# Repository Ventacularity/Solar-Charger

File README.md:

# Solar Charger

Solar-powered Li-ion charging and power management system implemented on a custom PCB.

## Overview
This project focuses on hardware design for managing variable solar input while safely charging a Li-ion battery and delivering regulated power rails. The system integrates dedicated charge controllers, buck/boost DC-DC converters, and an ESP32 for monitoring and control.

## Key Features
- Custom PCB design for solar-powered Li-ion charging
- Buck and boost DC-DC converters for regulated 5 V and 3.3 V outputs
- Battery voltage/current sensing and power-path management
- ESP32-based monitoring and control logic

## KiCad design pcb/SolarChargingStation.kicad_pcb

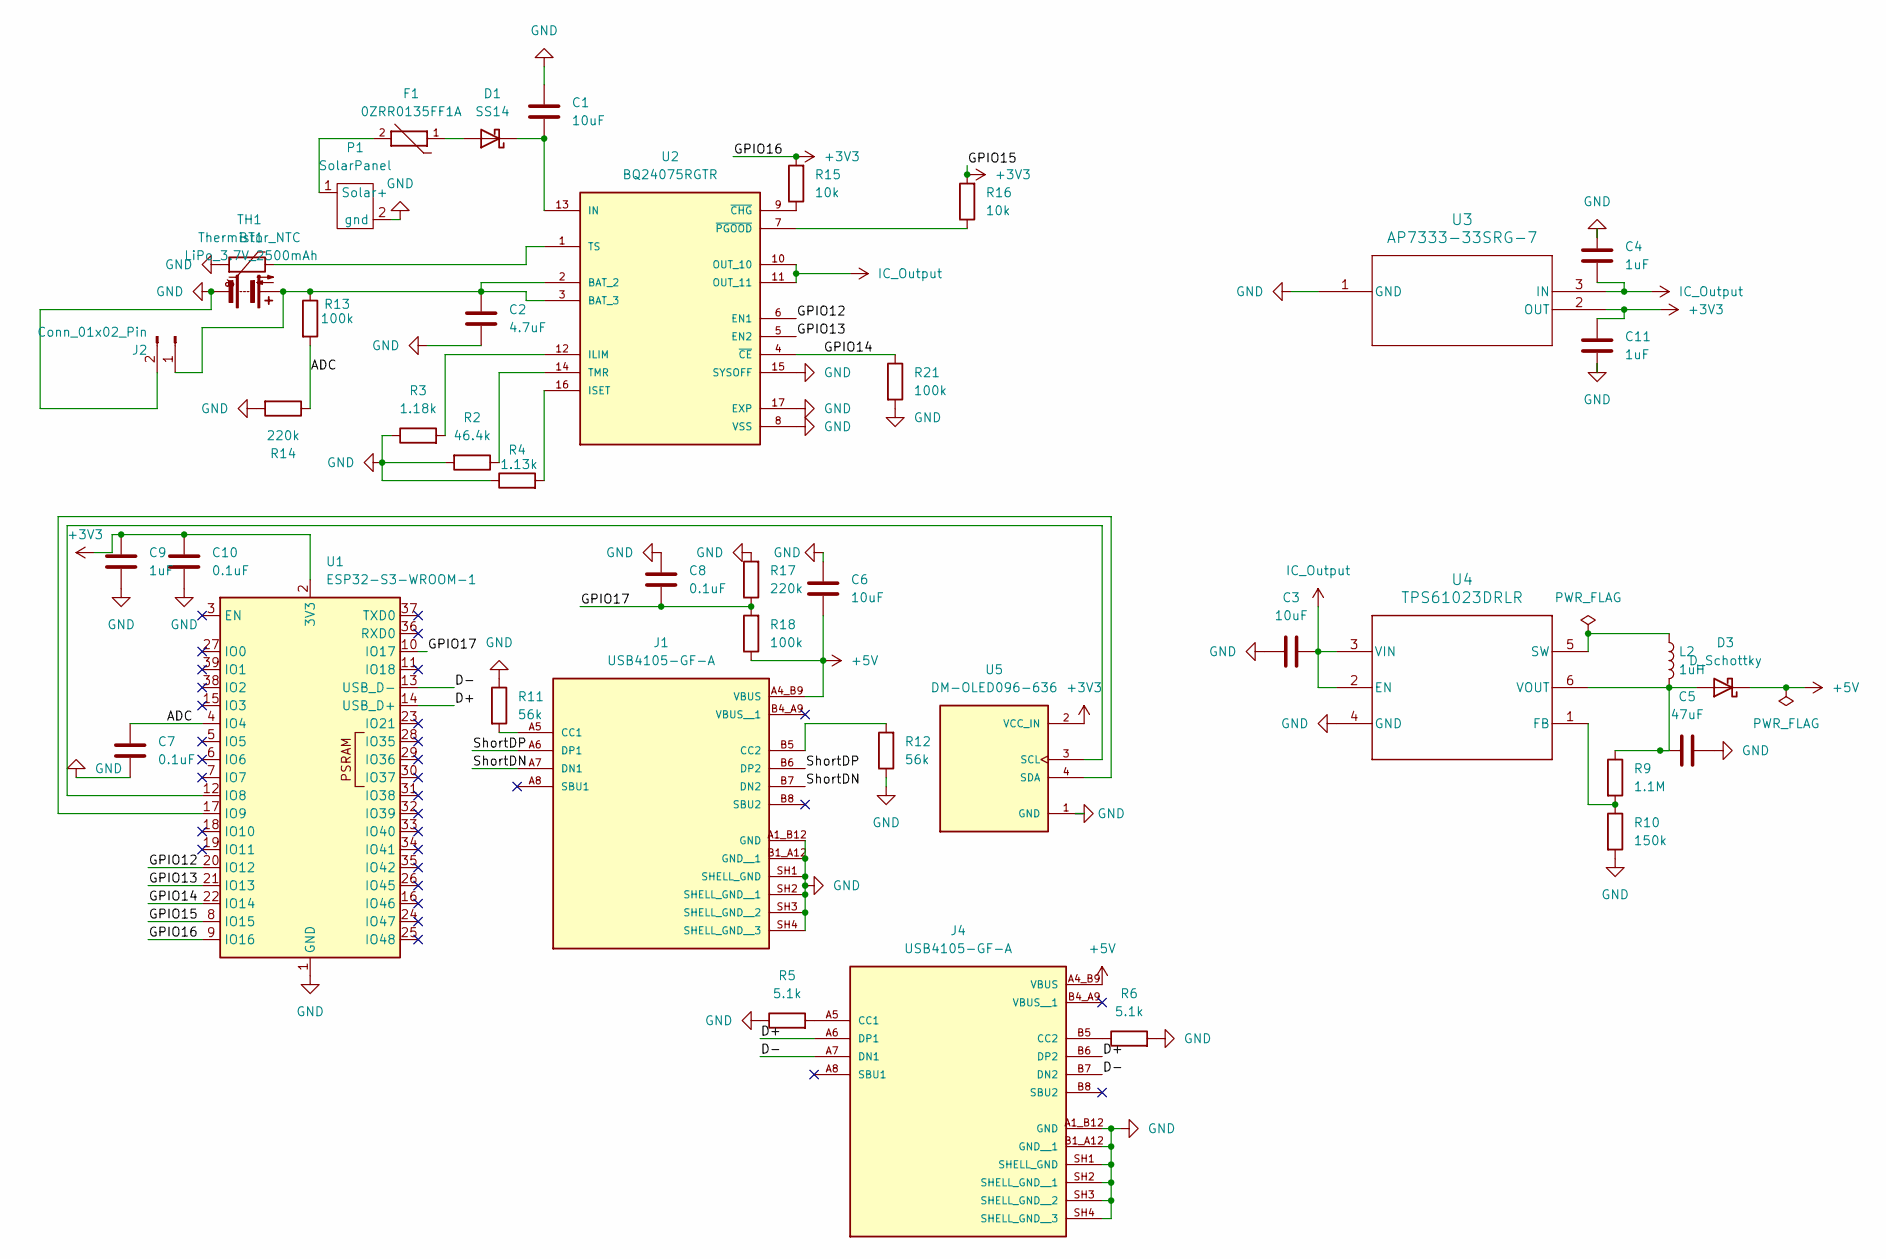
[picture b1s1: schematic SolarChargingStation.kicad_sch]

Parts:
BT1: LiPo_3.7V_2500mAh; JST_PH_B2B-PH-K_1x02_P2.00mm_Vertical
C1, C3, C6: 10uF; C_0805_2012Metric
C2: 4.7uF; C_0805_2012Metric
C4, C9, C11: 1uF; C_0805_2012Metric
C5: 47uF; C_0805_2012Metric
C7, C8, C10: 0.1uF; C_0805_2012Metric
D1: SS14; D_0805_2012Metric
D3: D_Schottky; D_0805_2012Metric
F1: 0ZRR0135FF1A; TRES_CMF0805_CTM; PARTREV Apr2023
J1, J4: USB4105-GF-A; GCT_USB4105-GF-A; PARTREV B4
J2: Conn_01x02_Pin; JST_PH_B2B-PH-K_1x02_P2.00mm_Vertical
L2: 1uH; L_0805_2012Metric
P1: SolarPanel; NewNewPanel
R2: 46.4k; R_0805_2012Metric
R3: 1.18k; R_0805_2012Metric
R4: 1.13k; R_0805_2012Metric
R5, R6: 5.1k; R_0805_2012Metric
R9: 1.1M; R_0805_2012Metric
R10: 150k; R_0805_2012Metric
R11, R12: 56k; R_0805_2012Metric
R13, R18, R21: 100k; R_0805_2012Metric
R14, R17: 220k; R_0805_2012Metric
R15, R16: 10k; R_0805_2012Metric
TH1: Thermistor_NTC; TRES_CMF0805_CTM
U1: ESP32-S3-WROOM-1
U2: BQ24075RGTR; QFN50P300X300X100-17N; PARTREV M
U3: AP7333-33SRG-7; SOT23R_DIO
U4: TPS61023DRLR; DRL0006A
U5: DM-OLED096-636; MODULE_DM-OLED096-636; PARTREV 2018-09-10

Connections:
+3V3: C9.1, C10.1, C11.1, R15.2, R16.2, U1.2 (3V3), U1.8 (IO15), U1.9 (IO16), U3.2 (OUT), U5.2 (VCC_IN)
+5V: C6.1, D3.1 (K), J1.A4_B9 (VBUS), J4.A4_B9 (VBUS), R18.1
/ADC: C7.1, R13.2, R14.1, U1.4 (IO4)
/D+: J4.A6 (DP1), J4.B6 (DP2), U1.14 (USB_D+)
/D-: J4.A7 (DN1), J4.B7 (DN2), U1.13 (USB_D-)
/GPIO12: U1.20 (IO12), U2.6 (EN1)
/GPIO13: U1.21 (IO13), U2.5 (EN2)
/GPIO14: R21.1, U1.22 (IO14), U2.4 (~CE)
/GPIO17: C8.1, R17.1, R18.2, U1.10 (IO17)
/ShortDN: J1.A7 (DN1), J1.B7 (DN2)
/ShortDP: J1.A6 (DP1), J1.B6 (DP2)
GND: BT1.2 (-), C1.1, C2.2, C3.1, C4.1, C5.1, C6.2, C7.2, C8.2, C9.2, C10.2, C11.2, J1.A1_B12 (GND), J1.B1_A12 (GND__1), J1.SH1 (SHELL_GND), J1.SH2 (SHELL_GND__1), J1.SH3 (SHELL_GND__2), J1.SH4 (SHELL_GND__3), J2.2, J4.A1_B12 (GND), J4.B1_A12 (GND__1), J4.SH1 (SHELL_GND), J4.SH2 (SHELL_GND__1), J4.SH3 (SHELL_GND__2), J4.SH4 (SHELL_GND__3), P1.2 (gnd), R2.2, R3.1, R4.1, R5.1, R6.2, R10.2, R11.1, R12.1, R14.2, R17.2, R21.2, TH1.1, U1.1 (GND), U1.40 (GND), U1.41 (GND), U2.8 (VSS), U2.15 (SYSOFF), U2.17 (EXP), U2.18, U2.19, U2.20, U2.21, U2.22, U3.1 (GND), U4.4 (GND), U5.1 (GND)
IC_Output: C3.2, C4.2, U2.10 (OUT_10), U2.11 (OUT_11), U3.3 (IN), U4.2 (EN), U4.3 (VIN)
unnamed: BT1.1 (+), C2.1, J2.1, R13.1, U2.2 (BAT_2), U2.3 (BAT_3)
unnamed: D1.2 (A), F1.1
unnamed: C1.2, D1.1 (K), U2.13 (IN)
unnamed: C5.2, D3.2 (A), L2.2, R9.1, U4.6 (VOUT)
unnamed: J1.A5 (CC1), R11.2
unnamed: J1.B5 (CC2), R12.2
unnamed: J4.A5 (CC1), R5.2
unnamed: J4.B5 (CC2), R6.1
unnamed: F1.2, P1.1 (Solar+)
unnamed: U1.12 (IO8), U5.3 (SCL)
unnamed: U1.17 (IO9), U5.4 (SDA)
unnamed: R3.2, U2.12 (ILIM)
unnamed: R4.2, U2.16 (ISET)
unnamed: R2.1, U2.14 (TMR)
unnamed: TH1.2, U2.1 (TS)
unnamed: R15.1, U2.9 (~CHG)
unnamed: R16.1, U2.7 (~PGOOD)
unnamed: R9.2, R10.1, U4.1 (FB)
unnamed: L2.1, U4.5 (SW)

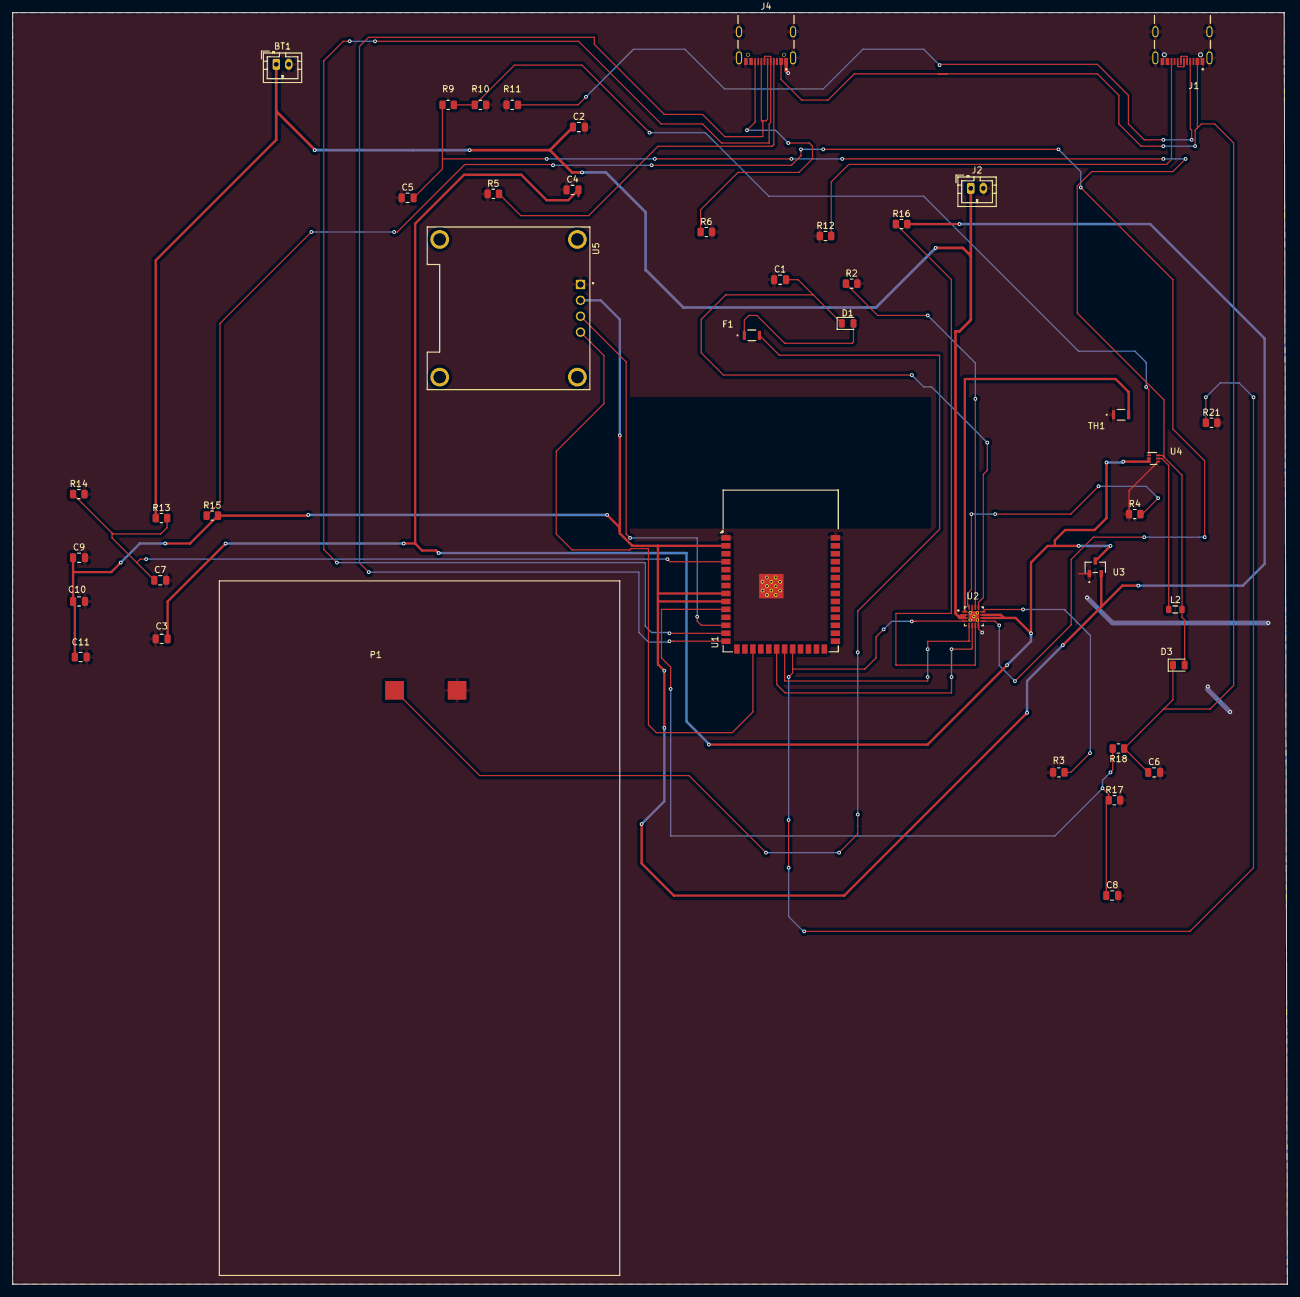
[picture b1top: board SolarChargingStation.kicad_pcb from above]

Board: 2 copper layers, 203.7 x 203.2 mm, 42 parts (0 on the bottom side), 32 nets.

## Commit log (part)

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2025-12-24 Revise README for Solar Charger project
    Updated project description and added key features and technologies.
2025-12-24 Refactor README to remove duplicate ESP32 mention
    Removed duplicate mention of ESP32-based monitoring and control logic from the Key Features section and updated the Tools & Technologies section.
2025-12-24 add charger
2025-12-24 add ESP32 Arduino firmware for solar charger
